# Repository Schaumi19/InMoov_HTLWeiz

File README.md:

# InMoov_HTLWeiz

### Motor Controller Pinout:

|   Motor   |      Sensor     |     PWM    |    Dir    |           
|-----------|-----------------|------------|-----------|
|     M1    |     S1 -> A0    |     D10    | D12 + D13 |
|     M2    |     S2 -> A1    |     D9     | D11 + D8  |
|     M3    |     S3 -> A2    |     D6     | D5 + D7   |
|     M4    |     S4 -> A6    |     D3     | D4 + D2   |

LED_Pin: A3
I2C_Pins: A4,A5

### Stuff to do:

#### Software(Andrea):
*
     - [ ] Skeleton tracking
     - [ ] Nuitrack stability
     - [ ] auto cam select
     - [X] Gesture recognition
     - [X] Follow me
     - [X] Speech recognition
	 - [ ] new gestures
     
####	New software-core IO(Thomas):
*	Out:
     - [X] Servo/Actuators
     - [X] Speech/Sounds
     - [ ] Mobility
     - [X] Connected Actuator Boards
     - [ ] Actuator Angles (Maybe Visu)
*	IN: 
     - [X] Speech
     - [ ] Position
     - [ ] Distance/Angle to Obstacle
     - [X] Distance/Angle to Person
     - [ ] Distance/Angle/Height of Object
     - [ ] Gyro Data for stabilization
*	Pre-Input: (befor progam start)
     - [X] gestures/Commands
     - [X] Voice Lines / text to speech
     - [X] Operation Limits (Virtual Border)

####	Electrical/AktuatorCode(Schaumi):
*
     - [X] Actuator-Boards more 5V Power
     - [X] New Motor Controller PCB
	 - [X] Electrical Error Detection(Pulldowns missing)
	 - [X] Mechanical Error Detection
	 - [X] Poti reverse
	 - [ ] Disable slowspeed upwards
     - [ ] Collision avoidance Lidar or Camera
     - [ ] Floor detection/fall down steps avoidance
     - [ ] Gyro-Sensor (Chest) (tip prevention) [maybe]
     - [X] noise filters for all motors

####	Mechanical(Rauber):
*
     - [ ] Shoulder out-Actuator
     - [X] Laptop holder
     - [X] Omni-wheels
     - [ ] better omni-wheels
     - [X] Arc - Reactor
     - [X] Instalation of Potis
     - [X] Lubrication of Gearboxes
     - [ ] print replacement parts with better materials/spezifications
  
#### Connections:
     Shoulders:
               1. Außi Aktuator
               2. Rotate UP-Down
               3. Rotate In-Out
               4. Bizeps/Trizeps
     Torso:
          1. Roll
          2. Rotate
          3. ARC-Reaktor

#### Protocols:
*
     - InMoovACP (Arduino Connect Protocol):
          - 2 Bytes <- Protocol length
          - 1st Byte:
            - 1 = BoardMotorController,
            - 2 = RGB,
            - 3 = Left hand side,
            - 4 = Middle,
            - 5 = Right hand side
          - 2nd Byte:
            - 0 = not Used (if 1st Byte is 1 or 2)
            - 1 = Hand,
            - 2 = Head,
            - 3 = Actuator (since there is max one per side)

*
     - InMoovAATP (Actuator Angle Transfer Protocol):
          - ;
          - Servo/Motor number(0 = All)
          - ,
          - Angle of Servo/Motor

          Example:	;0,90 --> All to 90
			;1,180 --> Ak. 1 to 180
*
     - New backwards compatible InMoovAATP (Actuator Angle Transfer Protocol):
          - ;
	  - AktuatorPlatine Nummer
			- 1 - linke Hand
			- 2 - linke Schulter
			- 3 - rechte Hand
			- 4 - rechte Schulter
			- 5 - Torso
			- 6 - Head
			- 7 - Board
			- 8 - RGB-Stripe
          - Servo/Motor number(0 = All)
          - ,
          - Angle of Servo/Motor

               Example:	;10,90 --> Linke hand All to 90
			          ;41,180 --> rechte Schulter Ak. 1 to 180
          Board: ;MotorSpeed1,MotorSpeed2
          RGB: R+R/C/O+Parameter
               Example: RR1 = RGB-Stripe, Rainbow, 1ms RainbowWaitTime
                        RC1,55,33,1 = RGB-Stripe, ColorWipe, red,green,blue,colorWipeTime
                        RO = RGB-Stripe, off
#### Terminal
*
     - serial_arr indexes:
          - 0 -> Board
          - 1 -> RGB
          - 2 -> Left Hand
          - 3 -> Left Actuator
          - 4 -> Head
          - 5 -> Middle Actuator
          - 6 -> Right Hand
          - 7 -> Right Actuator

#### Serial Arduino assignment
*
     - Kopf: 
          - 1 -> Auf/Ab
          - 2 -> Neigen
          - 3 -> NO FUNCTION
          - 4 -> Drehen
          - 5 -> Rechtes Auge
          - 6 -> Linkes Auge

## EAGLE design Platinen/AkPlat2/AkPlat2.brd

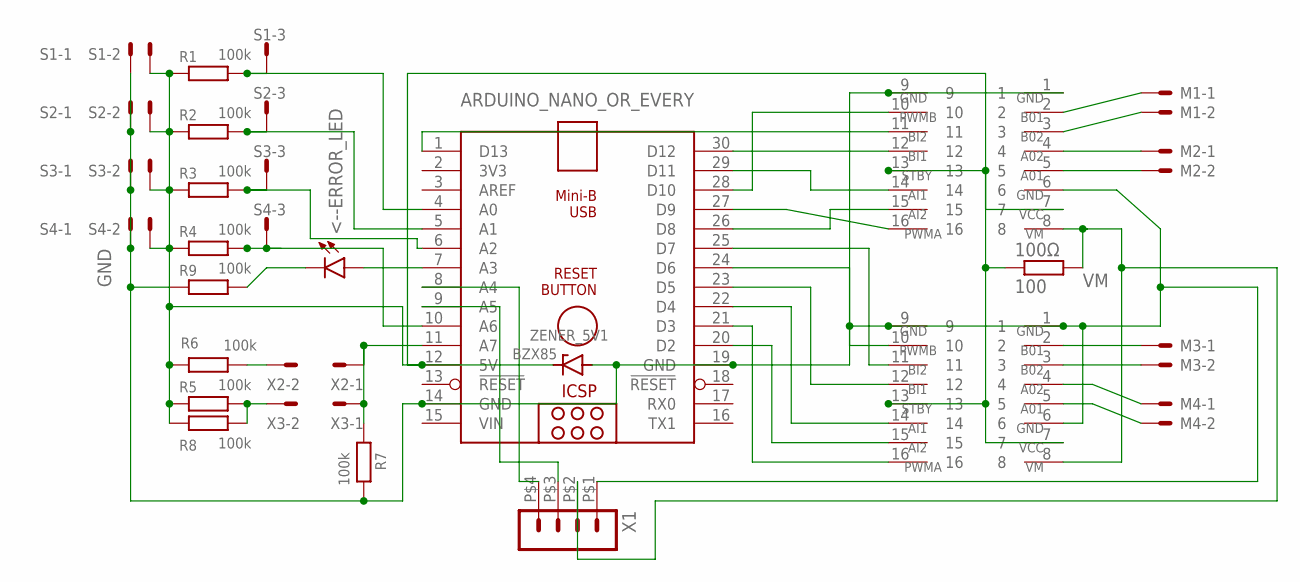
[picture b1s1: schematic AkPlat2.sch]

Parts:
100Ω: 100; 0204/7
<--ERROR_LED: LED3MM
ARDUINO_NANO_OR_EVERY: ARDUINO_NANO
M1, M2, M3, M4: 22-23-2021
R1, R2, R3, R4, R5, R6, R7, R8, R9: 100k; R0402
S1, S2, S3, S4: 22-23-2031
U$1, U$2: CONTROLLER
X1: HEADER_POS4_43045-0412; 43045-0412
X2, X3: 332-02
ZENER_5V1: BZX85; DO41Z10

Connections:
5V: 100Ω.1, ARDUINO_NANO_OR_EVERY.12 (5V), R1.1, R2.1, R3.1, R4.1, R5.1, R6.2, R8.1, S1.2, S2.2, S3.2, S4.2, U$1.7, U$1.13, U$2.7, U$2.13, ZENER_5V1.C
BIN2: ARDUINO_NANO_OR_EVERY.1 (D13), U$1.11
GND: ARDUINO_NANO_OR_EVERY.14 (GND), ARDUINO_NANO_OR_EVERY.19 (GND), R7.2, R9.1, S1.1, S2.1, S3.1, S4.1, U$1.1, U$1.6, U$1.9, U$2.1, U$2.6, U$2.9, X1.P$1 (1), ZENER_5V1.A
unnamed: ARDUINO_NANO_OR_EVERY.8 (A4), X1.P$4 (4)
unnamed: ARDUINO_NANO_OR_EVERY.9 (A5), X1.P$3 (3)
unnamed: ARDUINO_NANO_OR_EVERY.27 (D9), U$1.16
unnamed: ARDUINO_NANO_OR_EVERY.25 (D7), U$2.11
unnamed: ARDUINO_NANO_OR_EVERY.30 (D12), U$1.12
unnamed: ARDUINO_NANO_OR_EVERY.28 (D10), U$1.10
unnamed: ARDUINO_NANO_OR_EVERY.29 (D11), U$1.14
unnamed: ARDUINO_NANO_OR_EVERY.11 (A7), R7.1, X2.1, X3.1
unnamed: ARDUINO_NANO_OR_EVERY.26 (D8), U$1.15
unnamed: ARDUINO_NANO_OR_EVERY.24 (D6), U$2.10
unnamed: ARDUINO_NANO_OR_EVERY.21 (D3), U$2.16
unnamed: ARDUINO_NANO_OR_EVERY.20 (D2), U$2.15
unnamed: ARDUINO_NANO_OR_EVERY.22 (D4), U$2.14
unnamed: ARDUINO_NANO_OR_EVERY.23 (D5), U$2.12
unnamed: R6.1, X2.2
unnamed: M1.1, U$1.2
unnamed: M1.2, U$1.3
unnamed: M2.1, U$1.4
unnamed: M2.2, U$1.5
unnamed: M3.1, U$2.2
unnamed: M3.2, U$2.3
unnamed: M4.1, U$2.4
unnamed: M4.2, U$2.5
unnamed: R5.2, R8.2, X3.2
unnamed: <--ERROR_LED.A, ARDUINO_NANO_OR_EVERY.7 (A3)
unnamed: <--ERROR_LED.K (C), R9.2
unnamed: ARDUINO_NANO_OR_EVERY.10 (A6), R4.2, S4.3
unnamed: ARDUINO_NANO_OR_EVERY.6 (A2), R3.2, S3.3
unnamed: ARDUINO_NANO_OR_EVERY.5 (A1), R2.2, S2.3
unnamed: ARDUINO_NANO_OR_EVERY.4 (A0), R1.2, S1.3
VIN: ARDUINO_NANO_OR_EVERY.15 (VIN)
VM: 100Ω.2, U$1.8, U$2.8, X1.P$2 (2)

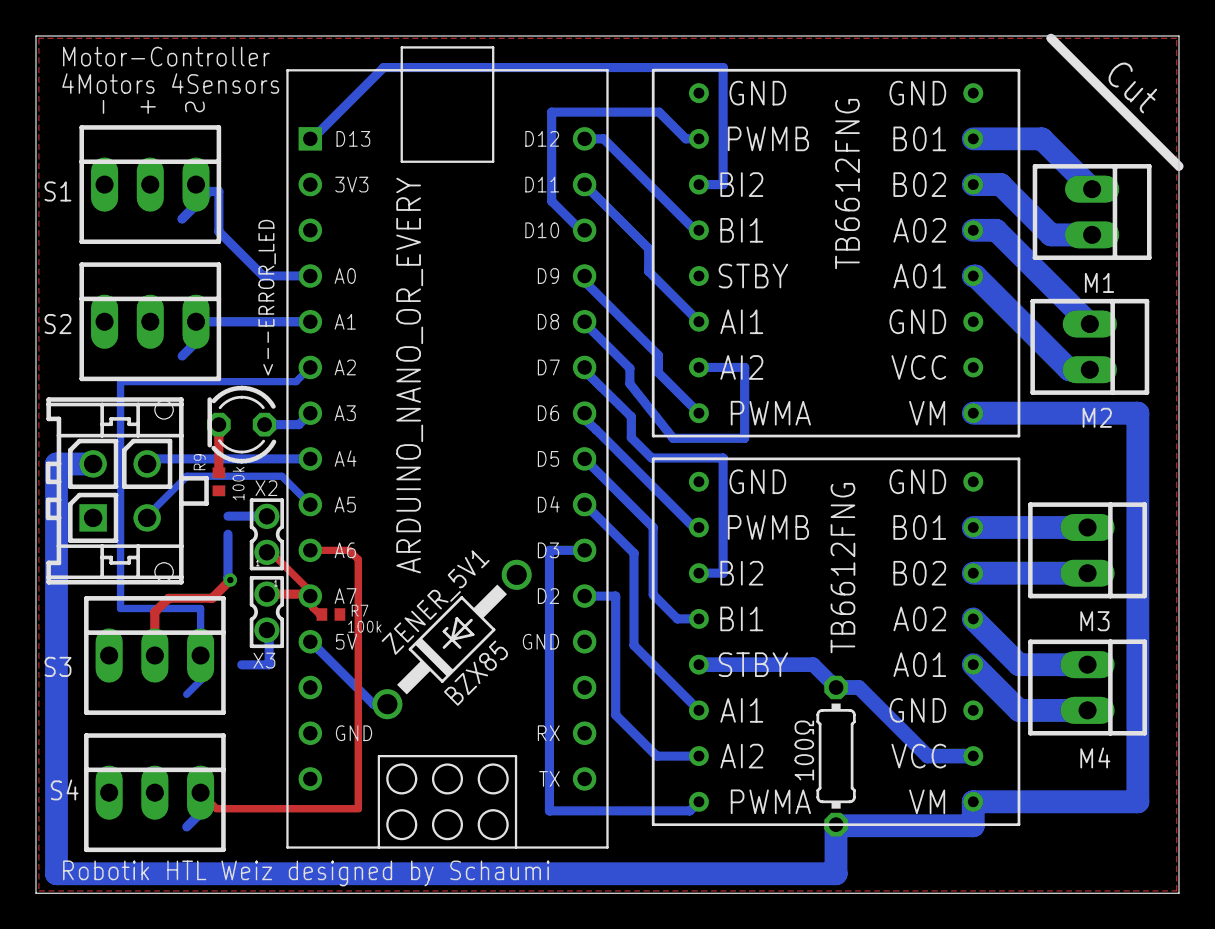
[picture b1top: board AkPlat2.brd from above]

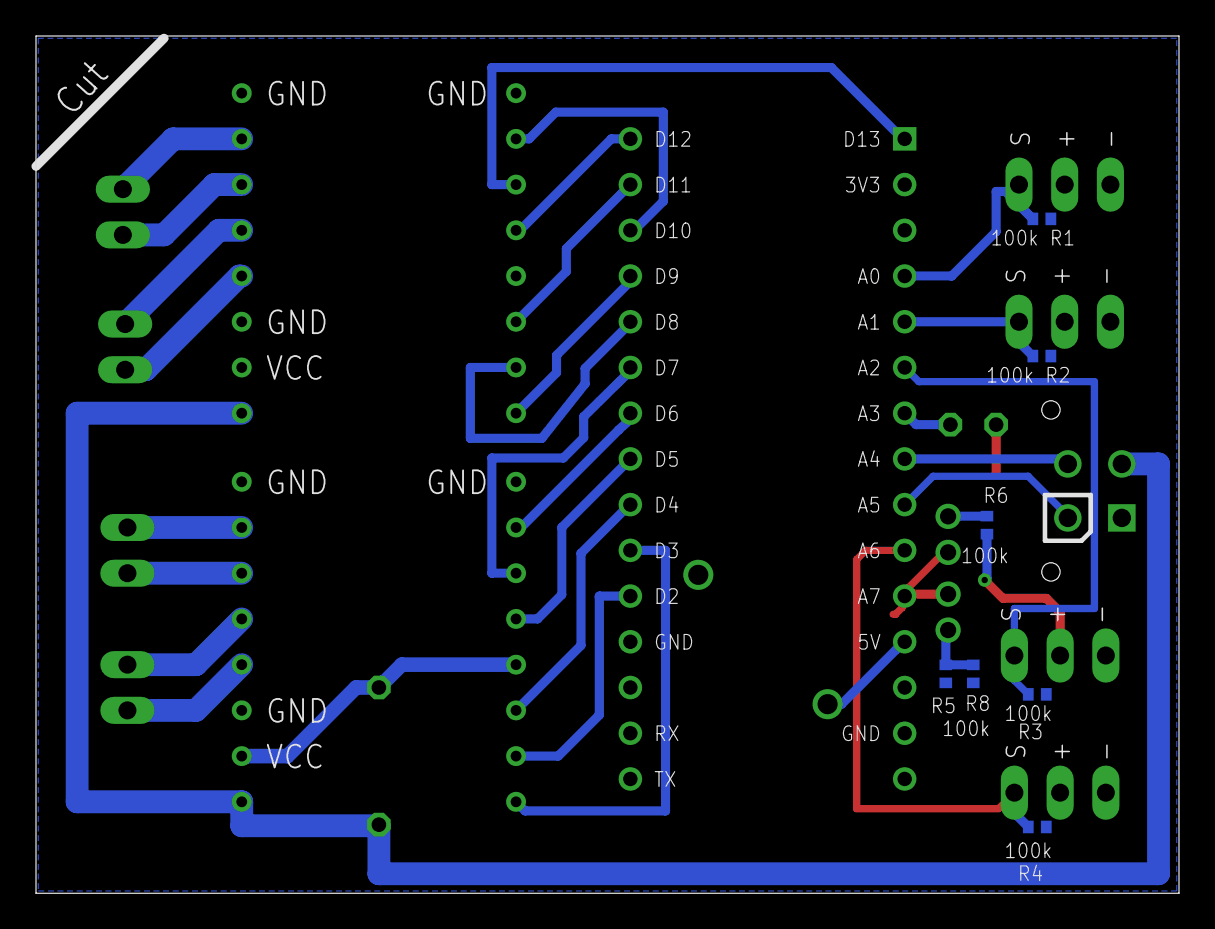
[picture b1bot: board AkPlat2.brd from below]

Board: 2 copper layers, 63.5 x 47.6 mm, 26 parts (7 on the bottom side), 34 nets.

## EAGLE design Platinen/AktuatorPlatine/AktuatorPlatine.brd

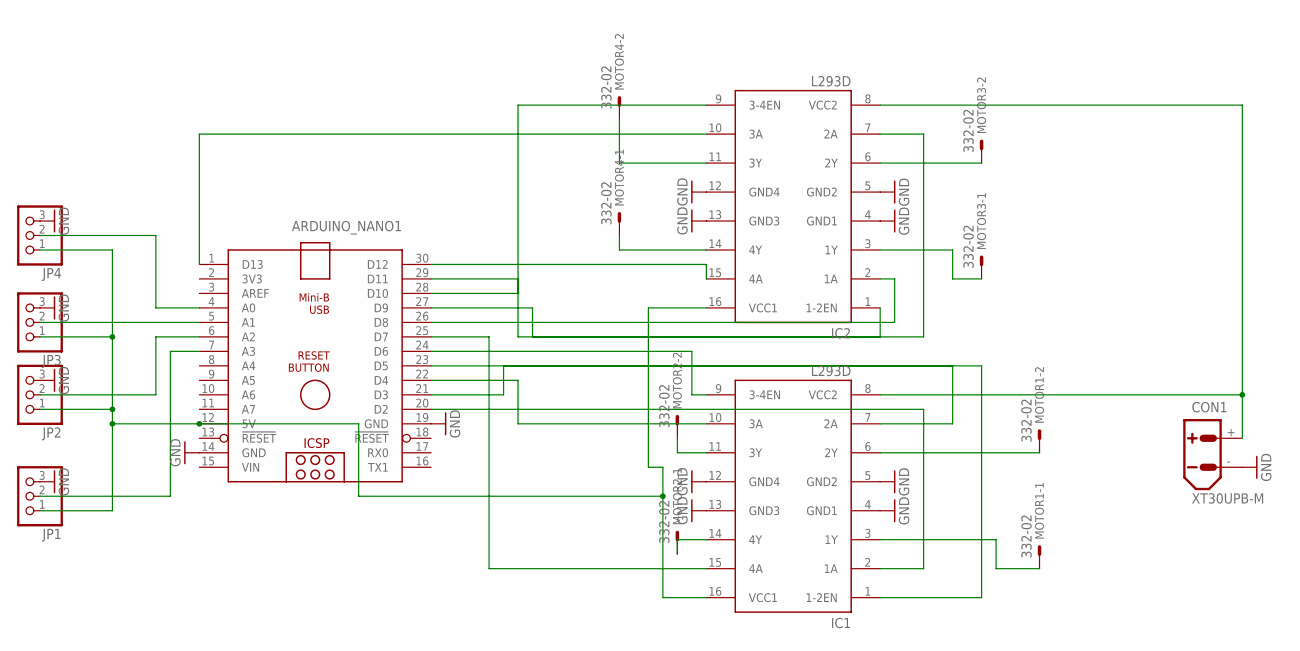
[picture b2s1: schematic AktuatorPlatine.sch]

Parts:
ARDUINO_NANO1: ARDUINO_NANO
CON1: XT30UPB-M
IC1, IC2: L293D; DIL16
JP1, JP2, JP3, JP4: PINHD-1X3; 1X03
MOTOR1, MOTOR2, MOTOR3, MOTOR4: 332-02

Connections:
GND: ARDUINO_NANO1.14 (GND), ARDUINO_NANO1.19 (GND), CON1.-, IC1.4 (GND1), IC1.5 (GND2), IC1.12 (GND4), IC1.13 (GND3), IC2.4 (GND1), IC2.5 (GND2), IC2.12 (GND4), IC2.13 (GND3), JP1.3, JP2.3, JP3.3, JP4.3
unnamed: ARDUINO_NANO1.20 (D2), IC1.2 (1A)
unnamed: ARDUINO_NANO1.21 (D3), IC1.7 (2A)
unnamed: ARDUINO_NANO1.22 (D4), IC1.10 (3A)
unnamed: ARDUINO_NANO1.23 (D5), IC1.1 (1-2EN)
unnamed: ARDUINO_NANO1.24 (D6), IC1.9 (3-4EN)
unnamed: ARDUINO_NANO1.27 (D9), IC2.1 (1-2EN)
unnamed: ARDUINO_NANO1.25 (D7), IC1.15 (4A)
unnamed: ARDUINO_NANO1.28 (D10), IC2.9 (3-4EN)
unnamed: ARDUINO_NANO1.26 (D8), IC2.2 (1A)
unnamed: ARDUINO_NANO1.29 (D11), IC2.7 (2A)
unnamed: ARDUINO_NANO1.30 (D12), IC2.15 (4A)
unnamed: ARDUINO_NANO1.1 (D13), IC2.10 (3A)
unnamed: ARDUINO_NANO1.12 (5V), IC1.16 (VCC1), IC2.16 (VCC1), JP1.1, JP2.1, JP3.1, JP4.1
unnamed: CON1.+, IC1.8 (VCC2), IC2.8 (VCC2)
unnamed: ARDUINO_NANO1.4 (A0), JP4.2
unnamed: IC1.3 (1Y), MOTOR1.1
unnamed: IC1.6 (2Y), MOTOR1.2
unnamed: IC2.3 (1Y), MOTOR3.1
unnamed: IC2.6 (2Y), MOTOR3.2
unnamed: IC2.11 (3Y), MOTOR4.2
unnamed: IC2.14 (4Y), MOTOR4.1
unnamed: IC1.11 (3Y), MOTOR2.2
unnamed: IC1.14 (4Y), MOTOR2.1
unnamed: ARDUINO_NANO1.5 (A1), JP3.2
unnamed: ARDUINO_NANO1.6 (A2), JP2.2
unnamed: ARDUINO_NANO1.7 (A3), JP1.2
VIN: ARDUINO_NANO1.15 (VIN)

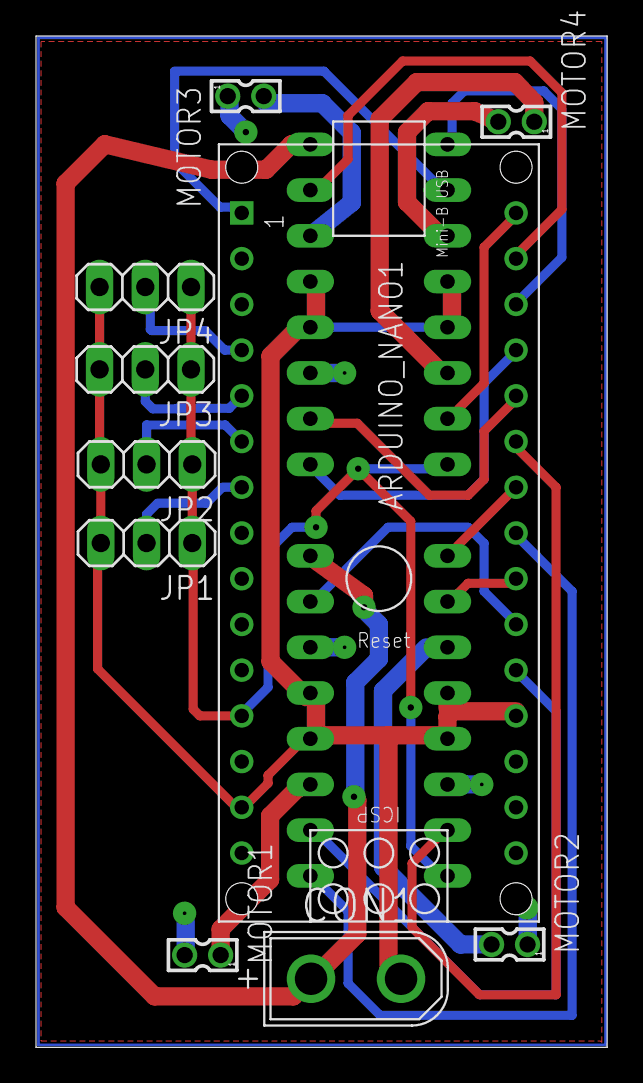
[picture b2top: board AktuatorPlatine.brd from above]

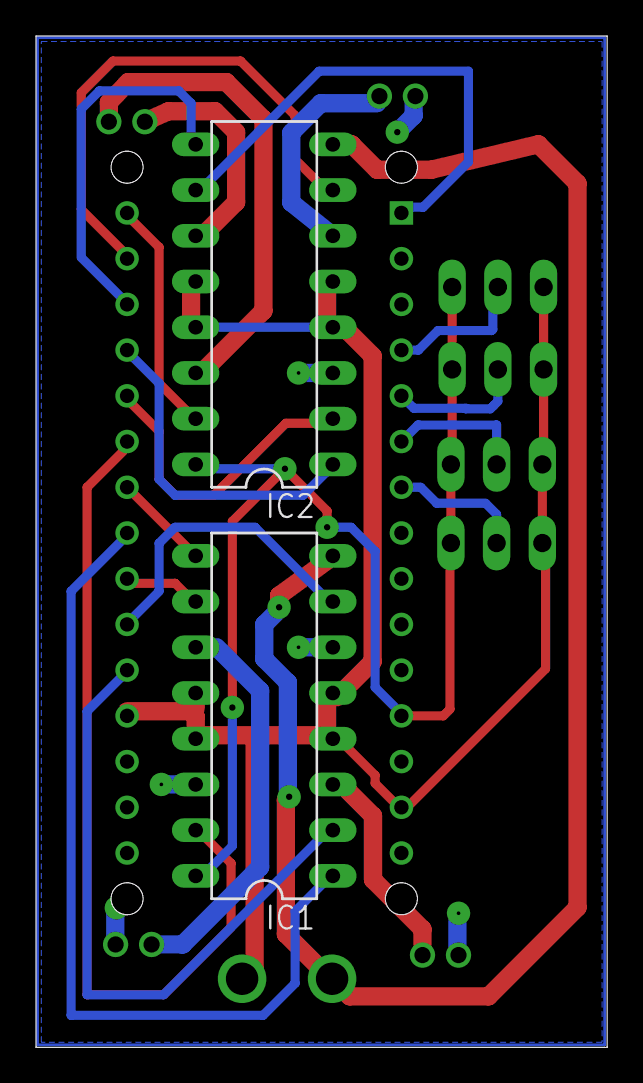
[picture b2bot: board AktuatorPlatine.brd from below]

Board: 4 copper layers, 31.7 x 56.2 mm, 12 parts (2 on the bottom side), 27 nets.

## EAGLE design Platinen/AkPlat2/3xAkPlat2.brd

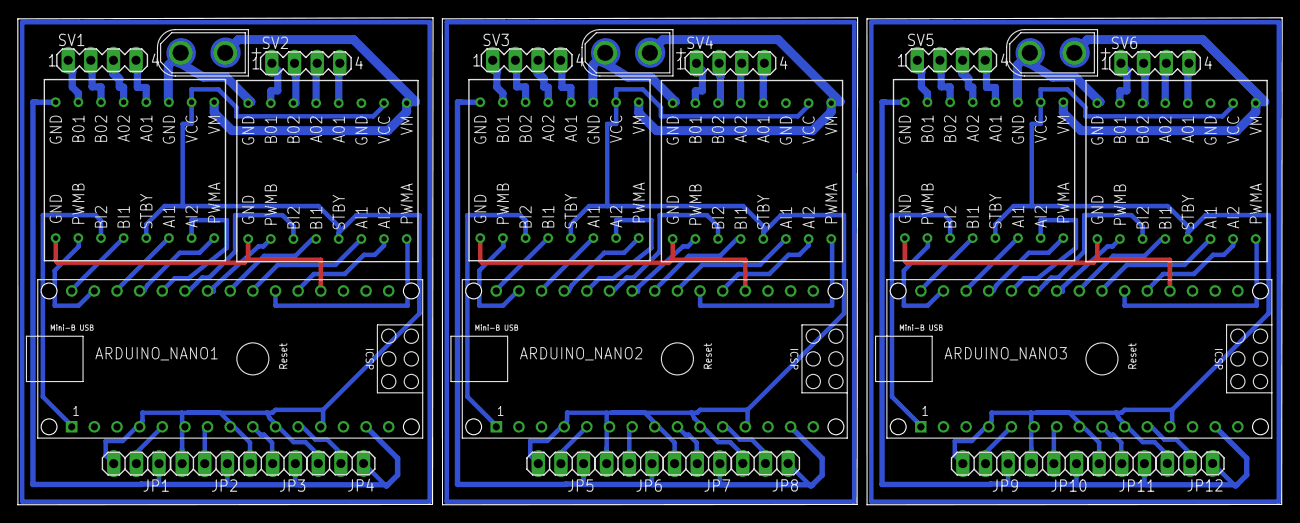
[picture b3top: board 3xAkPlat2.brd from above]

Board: 2 copper layers, 141.8 x 54.6 mm, 30 parts (0 on the bottom side), 87 nets.

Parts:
ARDUINO_NANO1, ARDUINO_NANO2, ARDUINO_NANO3: ARDUINO_NANO
CON1, CON2, CON3: XT30UPB-M
JP1, JP2, JP3, JP4, JP5, JP6, JP7, JP8, JP9, JP10, JP11, JP12: 1X03
SV1, SV2, SV3, SV4, SV5, SV6: MA04-1
U$1, U$2, U$3, U$4, U$5, U$6: CONTROLLER

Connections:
BIN1: ARDUINO_NANO2.1, U$3.11
BIN2: ARDUINO_NANO1.1, U$1.11
BIN3: ARDUINO_NANO3.1, U$5.11
unnamed: ARDUINO_NANO1.19, U$1.9, U$2.9
unnamed: CON1.-, U$1.6, U$2.1
unnamed: ARDUINO_NANO1.27, U$1.16
unnamed: ARDUINO_NANO1.25, U$2.11
unnamed: ARDUINO_NANO1.30, U$1.12
unnamed: ARDUINO_NANO1.29, U$1.10
unnamed: ARDUINO_NANO1.28, U$1.14
unnamed: CON1.+, U$1.8, U$2.8
unnamed: ARDUINO_NANO1.26, U$1.15
unnamed: ARDUINO_NANO1.24, U$2.10
unnamed: ARDUINO_NANO1.21, U$2.16
unnamed: ARDUINO_NANO1.20, U$2.15
unnamed: ARDUINO_NANO1.22, U$2.14
unnamed: ARDUINO_NANO1.23, U$2.12
unnamed: ARDUINO_NANO1.7, JP2.2
unnamed: SV1.1, U$1.2
unnamed: SV1.2, U$1.3
unnamed: SV1.3, U$1.4
unnamed: SV1.4, U$1.5
unnamed: SV2.1, U$2.2
unnamed: SV2.2, U$2.3
unnamed: SV2.3, U$2.4
unnamed: SV2.4, U$2.5
unnamed: ARDUINO_NANO1.14, JP1.1, JP2.1, JP3.1, JP4.1, U$1.1
unnamed: ARDUINO_NANO1.5, JP1.2
unnamed: ARDUINO_NANO1.9, JP3.2
unnamed: ARDUINO_NANO1.11, JP4.2
unnamed: ARDUINO_NANO1.12, JP1.3, JP2.3, JP3.3, JP4.3, U$1.7, U$1.13, U$2.7, U$2.13
unnamed: ARDUINO_NANO2.19, U$3.9, U$4.9
unnamed: ARDUINO_NANO2.30, U$3.12
unnamed: ARDUINO_NANO2.29, U$3.10
unnamed: ARDUINO_NANO2.27, U$3.16
unnamed: ARDUINO_NANO2.28, U$3.14
unnamed: ARDUINO_NANO2.26, U$3.15
unnamed: ARDUINO_NANO2.24, U$4.10
unnamed: ARDUINO_NANO2.21, U$4.16
unnamed: ARDUINO_NANO2.20, U$4.15
unnamed: ARDUINO_NANO2.22, U$4.14
unnamed: ARDUINO_NANO2.23, U$4.12
unnamed: ARDUINO_NANO2.25, U$4.11
unnamed: CON2.-, U$3.6, U$4.1
unnamed: CON2.+, U$3.8, U$4.8
unnamed: SV3.1, U$3.2
unnamed: SV3.2, U$3.3
unnamed: SV3.3, U$3.4
unnamed: SV3.4, U$3.5
unnamed: SV4.1, U$4.2
unnamed: SV4.2, U$4.3
unnamed: SV4.3, U$4.4
unnamed: SV4.4, U$4.5
unnamed: ARDUINO_NANO2.14, JP5.1, JP6.1, JP7.1, JP8.1, U$3.1
unnamed: ARDUINO_NANO2.5, JP5.2
unnamed: ARDUINO_NANO2.7, JP6.2
unnamed: ARDUINO_NANO2.9, JP7.2
unnamed: ARDUINO_NANO2.11, JP8.2
unnamed: ARDUINO_NANO2.12, JP5.3, JP6.3, JP7.3, JP8.3, U$3.7, U$3.13, U$4.7, U$4.13
unnamed: ARDUINO_NANO3.19, U$5.9, U$6.9
unnamed: ARDUINO_NANO3.30, U$5.12
unnamed: ARDUINO_NANO3.29, U$5.10
unnamed: ARDUINO_NANO3.27, U$5.16
unnamed: ARDUINO_NANO3.28, U$5.14
unnamed: ARDUINO_NANO3.26, U$5.15
unnamed: ARDUINO_NANO3.24, U$6.10
unnamed: ARDUINO_NANO3.21, U$6.16
unnamed: ARDUINO_NANO3.20, U$6.15
unnamed: ARDUINO_NANO3.22, U$6.14
unnamed: ARDUINO_NANO3.23, U$6.12
unnamed: ARDUINO_NANO3.25, U$6.11
unnamed: CON3.-, U$5.6, U$6.1
unnamed: CON3.+, U$5.8, U$6.8
unnamed: SV5.1, U$5.2
unnamed: SV5.2, U$5.3
unnamed: SV5.3, U$5.4
unnamed: SV5.4, U$5.5
unnamed: SV6.1, U$6.2
unnamed: SV6.2, U$6.3
unnamed: SV6.3, U$6.4
unnamed: SV6.4, U$6.5
unnamed: ARDUINO_NANO3.14, JP9.1, JP10.1, JP11.1, JP12.1, U$5.1
unnamed: ARDUINO_NANO3.5, JP9.2
unnamed: ARDUINO_NANO3.7, JP10.2
unnamed: ARDUINO_NANO3.9, JP11.2
unnamed: ARDUINO_NANO3.11, JP12.2
unnamed: ARDUINO_NANO3.12, JP9.3, JP10.3, JP11.3, JP12.3, U$5.7, U$5.13, U$6.7, U$6.13

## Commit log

2020-12-26 basic stuff 1
2020-12-28 Add files via upload
    28.12.2020
2020-12-28 28.12.2020
    Terminal V1.1
2020-12-28 28.12.2020
    Most importaint piece of code!
2021-01-24 24.01.2020
    fixed voice recognition engine
2021-02-12 upload MOtor config
2021-02-13 upload Vesc Controller
2021-02-14 VESC lib added
2021-02-14 VESC Read/Write workes again
2021-02-14 VESC Current change added
2021-02-14 new try
2021-02-16 Motor Tool Update + Firmware update
2021-03-23 new stuff
2021-03-23 TTGO(Display) stuff
2021-03-23 better MotorArduino
2021-03-23 TTGO stuff
2021-03-24 ttgo softserial
2021-03-24 Editor Version for the SerialPortTerminal
2021-03-24 Added a reload button
2021-04-21 Relayschaltung
2021-04-21 Neu sortiert und unnötiges gelöscht
2021-04-21 Add config File to Servocontroller
2021-04-21 change Baud_Rate
2021-04-21 Updated version
2021-04-27 updated Display to show stats of the motors and battery
2021-04-28 test
2021-04-28 robotic 28
2021-04-28 fixed display
2021-05-05 Baudrate
2021-05-11 Lowered the Acceleration to 1RPM/10ms
2021-05-23 Platine
2021-05-23 some stuff
2021-05-23 GBRs
2021-05-24 Platine pdfs
2021-05-25 Platinen stuff vom Prototype ätzen
2021-05-26 More clearance
2021-05-26 Test code finished
2021-06-07 platine neu
2021-06-07 some things got changed/fixed
2021-06-07 changed some things
2021-06-07 added steering
2021-06-07 board changes
2021-06-08 Display
2021-06-08 BLE in motorcontroller
2021-06-08 cleanup
2021-06-08 RGB cleanup
2021-06-14 platine verbessert
2021-06-14 akcode stuff
2021-06-23 changed sth.
2021-06-23 changed things
2021-06-29 Merge branch 'main' of https://github.com/Schaumi19/InMoov_HTLWeiz into main
    # Conflicts:
    # SerialPortTerminal/.vs/SerialPortTerminal/v16/.suo
    # SerialPortTerminal/SerialPortTerminal/obj/x86/Debug/SerialPortTerminal.csprojAssemblyReference.cache
2021-10-06 fixed
2021-10-13 works
2021-10-20 code done (nearly)
2021-10-20 finished
2021-11-10 semi-finished mk2
2021-11-10 semi-finished mk3
2021-12-03 Platinen Änderungen ewig her
2021-12-22 new joystick control 2.0
2022-01-12 finally fucking Aktuator works
2022-01-26 submission
2022-02-12 Platine changes and smother movement
2022-02-12 Palatine new plug alignment
2022-02-12 PCB almost done
2022-02-13 PCB fertig Gerber fertig
2022-02-13 Update README.md
    Added Pinout
    Added full ToDo
2022-02-13 just sorting some stuff and garbage collections
2022-02-15 cleaning up done
2022-02-16 added Upgrade Aktuator code to ToDo list
2022-02-17 started working on Terminal
2022-02-17 some improvements
2022-02-17 added protocols section
2022-02-21 getting there
2022-02-21 updated protocols
2022-02-21 added ACP implementation
2022-02-26 updated ACP
2022-02-26 added monitoring to terminal
2022-03-07 Data transfer and ACP fixes
2022-03-07 fuck u
2022-03-24 Hüft Servo Belegung/Range
2022-03-30 Added controls over terminal
2022-04-11 added some features
2022-04-12 added connect_all_ports and stuff
2022-04-12 added connect_all_ports
2022-04-19 19.04.2022 14:51
2022-04-19 fixed windows bugs
2022-04-19 windows fix
2022-04-19 Commit 19.04.2022 10:51
2022-04-19 19.04.2022 15:26
2022-04-19 boardchanges
2022-04-19 Schaumi changes
2022-04-19 moved code to different files
2022-04-19 some changes i forgot to save
2022-04-19 some changes
2022-04-20 Aktuator Code working. Short circuit breaking implemented. Comm testing missing
2022-04-20 some communictaion testing. not working
2022-04-20 follow me
2022-04-20 follow me added
2022-04-20 added gestures system and quit functionality
2022-04-20 no real changes
2022-04-20 some connection tests
2022-04-20 beforePull
2022-04-20 fixed ascii serial
2022-04-20 tried to fix
2022-04-20 aktuator finally working
2022-04-20 added RockPaperScissor + Websocket
2022-04-20 moved files for recognition
2022-04-20 no changes
2022-04-20 Preprossesor boardselect
2022-04-21 Aktuator Code: Advanced Debug modes Servocontroller: repair + Serial comm
2022-04-21 21.04.2022 14.10
2022-04-21 added time to live for board commands
2022-04-21 added routine
2022-04-21 RockPaperScissor communication
2022-04-21 Added InMoov support for Rock Paper Siccors
2022-04-21 All Aktuator limits set
2022-04-21 repair merge mess
2022-04-22 gitignore test
2022-04-22 gitignore testing2
2022-04-22 Added Continuous movement for stomach
2022-04-22 fixed problems with board
2022-04-22 perfected rps
2022-04-22 on stage
2022-04-22 version-freeze v1
2022-04-22 version-freeze v1.1
2022-04-22 version-freeze v1.1.1
2022-04-25 just testing
2022-04-26 Commit
    Commit
    Commit
    Commit
2022-04-26 better Speed control
2022-04-26 Implemented Error against electrical Wire break or short circuit
2022-04-26 Implemented Mechanical Error detection. Testing missing!!
2022-04-27 added skeletondata file
2022-05-04 added testing prints to follow_me
2022-05-04 merged follow_me and skeletonData
2022-05-04 debugging
2022-05-04 27.04.2022, 16.11
2022-05-10 created dev_sch branch
2022-05-11 updated menus
2022-05-11 Multi-Threaded ACP and fixed arduino-not-sending freeze
2022-05-11 Added ifdef ACP
2022-05-11 Updated up to current standards
2022-05-13 Debugging Error Detection
2022-05-17 Updated Transfer Protocol(AATP) + Implemented AATP into Kopf Code
2022-05-17 fixed some typos
2022-05-17 just sorting some stuff
2022-05-17 Working state update
2022-05-18 new keys program
2022-05-18 before_checkout
2022-05-18 changed README to have a new section
2022-05-18 Updated Head commands
2022-05-18 weird python caches
2022-05-18 follow_me updated
2022-05-23 Splitted Error to Error and TimeError
2022-05-25 Fixing error detec + Servo to Aktuator change
2022-05-25 added speechrecognition files
2022-05-25 before-merge
2022-05-25 small changes for release
2022-05-31 Fixed Serial support
2022-05-31 Added delay after connecting ports to check ACP
2022-05-31 Updated steering menu
2022-05-31 Fixed Joystick steering
2022-05-31 more error margin
2022-05-31 bug fix and more error margin
2022-05-31 updated RPS
2022-06-01 final changes before version freeze!
2022-06-01 changed Error border at Torso
2022-06-02 changed RockPaperScissors
2022-06-02 Technical interview
2022-06-02 after interview
2022-06-02 fixed intention on RockPaperScissors
2022-06-02 Added error config to the config
2022-06-02 merged follow_me and RPS
2022-06-02 added angelspeed to calculation to prevent overshooting
2022-06-02 follow_mw changes
2022-06-03 BeforeSchaumiDev
2022-06-04 added PID control
2022-06-04 merged PID-control
2022-06-15 Fixed some Typos + added commented AktuatorCode + renamed some variables
2022-06-15 switched to current Control
2022-06-15 follow_me usable in menu
2022-06-22 Changed back to RPM Control and startet calibration
2022-07-05 changed .gitignore to ignore .pyc files
2022-07-05 deleted some junk
2022-07-05 Changed PID because of Board PID change
2022-07-05 camera index testing
2022-07-05 changed actuator limits to safer values
2022-07-10 added voice lines to RockPaperScissors
2022-07-11 added voice lines to routine
2022-07-11 Cleaned up routine
2022-07-11 Cleaned up other code and added backup solutions for gestures
2022-07-11 Changed hand_tracking to use different camera
2022-07-11 Changed aktuator code to use more recent values
2022-07-11 changed follow_me pid
2022-07-11 added more gitignore
2022-07-12 final changes before world cup
2022-07-14 Added some Renderings
2022-07-14 Uploaded schematic
2022-07-14 Added some pics
2022-10-12 Motorcontroller Platine V3.0 finished
2022-10-18 Added Molex lbr and updated Readme Images
2022-10-18 Changed Readme Images
2022-10-18 revise BoardMotorController Code
2022-10-24 Revise RGB Code not finished
2022-11-07 Pre Robotic
2022-11-07 Updated Pinout
2022-11-09 adapted aktuator code for new board
2022-11-09 working version
2022-11-10 Added Reverse Input Funktion and solved Direction change Error Bug
2022-11-10 Updated ToDo List
2022-11-10 added dipl doku
2022-11-14 updated Middle Actuator Code
2022-11-17 Implemented I2C, functionality unkwnown
2022-11-19 some I2C testing
2022-11-19 I2C working, also with nano-every, need to be tested on live system
2022-11-19 added working times
2022-11-19 cleanup and small change
2022-11-22 added left ausi actuator
2022-11-22 improved external id finder
2022-11-30 added right ausi aktuator
2022-12-05 started splitting
2022-12-05 Added new Aktuator control Protokoll
2022-12-08 added header files
2022-12-10 started new, mostly finished
2022-12-10 Program compiles without Errors
2022-12-12 impelmented new object oriented Code into hand Code
2022-12-12 Fixed Bug: only 4 of the 6 Hand servos were usable
2022-12-12 Implemented object oriented Code into Kopf Code
2022-12-13 Some Bug fixes
2022-12-14 started with angular speed dev
2022-12-14 Implemented Angular Speed
2022-12-14 Bug fix
2022-12-14 splittet AngularSpeed --> fixed compiling error
2022-12-14 Solved Error detection bug
2022-12-18 started working on Aktuator Pos change
2022-12-18 Added Dir Error
2022-12-20 changed to makro parameters
2022-12-20 found and semi solved variable overwriting because of 96% dynamic memory use of the arduino nano 168
2023-01-18 Changed Pinout
2023-01-19 improvisation, code in CODE_HERE.py
2023-01-20 working I2C and basic gesture
2023-01-20 using ports
2023-01-23 added RPS gestures - not tested
2023-01-23 after Tag_der_offenen_Tür
2023-01-23 reverted changes
2023-01-26 Some successful Tests
2023-01-26 Added some HowTo files
2023-01-29 Actuator Config Tool Gui + Some Cleanup + EEPROM Test
2023-02-01 Added a few Test Codes but pre Testing
2023-02-06 Working py to arduino and back
2023-02-07 Config Connection Working
2023-02-10 AktuatorConfigTool mostly finished and implemented in AktuatorCode
2023-02-27 Config Read/Write and save/load from EEPROM working
2023-02-28 clean up but there are transfer bugs
2023-03-01 Transmit bug fixed
2023-03-01 finished,testing with hardware needed
2023-03-06 Added Install Guide
2023-03-06 bug fixes + added pos-select to config tool
2023-03-08 Doku
2023-03-08 Added Position eeprom saving
2023-03-15 AktuatorConfigTool tested debuged + working
2023-03-16 some cleanup and comments
2023-03-16 some cleanup
2023-03-16 bug fixes
2023-03-17 Implemented RBG control funktion unknown
2023-03-17 some updates
2023-03-19 dipl
2023-03-19 Added I2C Funktionality. Funktion unknown
2023-03-19 Added Continues movement speed control
2023-03-19 added connection list and some improvements
2023-03-19 Added Warning
2023-03-19 Added imgs
2023-03-20 Rps working, new gestures working
2023-03-20 added lables
2023-03-20 added RGB+Motor i2c + fixed Dir_Error Problem
2023-03-20 Added outOfRange Deadzone
2023-03-22 RGB-Code working except SC
2023-03-22 hotfix orderd by andrea
2023-03-22 Hotfix ordered by andrea
2023-03-22 Hotfix
2023-03-27 new recognition files, for dipl. & changes for RPS
2023-04-11 fixed Error in gestures
2023-04-12 Added RockPaperSissor Cliet for simple Terminal use
2023-04-12 file for testing camera index
2023-04-12 added question for camera index for RPS server
2023-04-14 changed imports for opencv
2023-04-17 changes in RPS_server
2023-04-19 minimal change in RPS file
2023-04-19 change in RPS
2023-04-19 Added code for detecting microphone index
2023-04-19 changed index for microphone
2023-04-19 changed noerr in RPS
2023-04-19 changed order in RPS server
2023-04-19 changed method for speech
2023-04-19 added setup files
2023-04-19 small changes in setup
2023-04-19 small changes
2023-04-19 added settings for camera index in rps server
2023-04-19 changed setup
2023-04-19 added .desktop files
2023-04-19 setup finished
2023-04-20 changed microphone function
2023-04-20 changed gestures
2023-04-20 deleted mp3 file
2023-04-20 imported sys
2023-06-12 last changes
